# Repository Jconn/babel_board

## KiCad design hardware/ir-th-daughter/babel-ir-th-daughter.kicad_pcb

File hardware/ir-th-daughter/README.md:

# Babel IR TH daughter board — revision A (hand-solder)

A version of the [IR daughter](../ir-daughter/README.md) that can be built with
a soldering iron. Same host interface, outline, carrier holes and bench header;
the sensor is a through-hole MLX90614 in a TO-39 can, and every other part has
iron-friendly pads. Routed, DRC 0/0. OSH Park zip:
[`../fab/oshpark/babel-ir-th-daughter-revA-oshpark.zip`](../fab/oshpark/).

Open hardware under **CC BY-SA 3.0**, as an adaptation of the IR daughter; see
[LICENSE](LICENSE).

## What's the same as the IR daughter (rev C)

- J1 card edge, pinout and outline: VDD on contacts 3 and 18, GND on 1, 2, 8,
  19, 20; NVM bus on 5/6/7; sensor bus on 9/10. Reversible in the radio.
- J2 2x4 bench header, same pinout and position (see the IR daughter README).
- 24LC256 EEPROM at 0x50 with WP held high by R1; R2-R5 bus pull-ups DNP.
- 2 mm rounded body corners, chamfered tongue shoulders, carrier holes H1/H2.

## What's different

| | IR daughter rev C | IR TH daughter rev A |
| --- | --- | --- |
| Sensor | MLX90632 (3 x 3 mm leadless, bottom pad) | MLX90614ESF-BCC-000-TU (TO-39, 4 leads) |
| Sensor address | 0x3A | 0x5A (SMBus, 100 kHz max) |
| Accuracy | about ±0.2 °C (medical range) | about ±0.5 °C |
| Field of view | about 50° | 35° |
| Host maths | Host computes temperature from calibration data | Sensor reports object/ambient temperature directly |
| Passives | 0603 | 0805 hand-solder pads |
| ADDR resistor (R6) | Yes | None (address is in sensor EEPROM) |

The host must use an MLX90614 driver for this card; the MLX90632 driver does
not work with it. The sensor bus pins are unchanged, so the radio needs no
change.

## Circuit

- U1: MLX90614ESF-BCC-000-TU, 3 V part (2.6-3.6 V), gradient compensated,
  35° field of view. TO-39 pins (Melexis datasheet rev 021, figure 1): 1 SCL,
  2 SDA, 3 VDD, 4 VSS. The can connects only to VSS internally; nothing else
  touches it. KiCad `TO-39-4` pad numbers match the datasheet with the tab at
  the upper left, as silkscreened.
- C1 100 nF beside U1 pins 3/4 (Melexis recommends 100 nF close to the sensor).
- U2 24LC256 (SOIC-8, 1.27 mm pitch: easy with an iron), C2 at its supply pin,
  C3 1 µF at the port, R1 10k WP pull-up.

## Assembly by hand

What to buy (three boards plus spares, and the ESP32-S3 bench kit):
[purchase-bom.csv](purchase-bom.csv). `bom.csv` is the generated design BOM.

1. Start with the smallest parts: U2 (tack one corner pin, check alignment,
   then the rest), then the 0805 passives. Leave R2-R5 off unless this card
   will run on a bench host without pull-ups.
2. U1 last on the front: insert with the tab matching the silk notch, keep
   the can square to the board, solder from the back, and trim the leads flush
   (under 1 mm). The carrier's 10 mm relief hole sits behind the leads.
3. J2 only on bench cards; it does not fit the host boot or carrier.

Power from a current-limited 3.3 V supply first. An I2C scan should show 0x5A
(sensor) and 0x50 (EEPROM).

## Mechanical notes

- The TO-39 can stands about 4-5 mm off the front face (a can, not a flat
  package). Keep it clear of anything in front of the card and keep the 35°
  field of view open.
- Through-hole leads come out on the back inside the carrier's sensor relief.
- The boot-slot interference with U2/R1/C3 noted in `../ROUTING.md` applies to
  this board too (same positions).

## Checks and reproduction

```sh
K=squashfs-root/bin/kicad-cli; D=hardware/ir-th-daughter
python3 $D/tools/generate_schematic.py
$K sch erc $D/babel-ir-th-daughter.kicad_sch --exit-code-violations -o $D/erc-report.txt
$K sch export netlist $D/babel-ir-th-daughter.kicad_sch --format kicadxml -o $D/babel-ir-th-daughter.net.xml
python3 $D/tools/verify_netlist.py
$K pcb drc --schematic-parity --severity-error --severity-warning --format json \
    -o $D/layout-routing-drc.json $D/babel-ir-th-daughter.kicad_pcb
```

DRC: 0 violations, 0 unconnected, with the same two excluded J2 silk-corner
markers as the IR daughter. Schematic parity lists H1/H2 as board-only
footprints (carrier holes), as on the IR daughter.

Not tested: fabrication, hand assembly, sensor readings, carrier fit with the
TO-39 can.

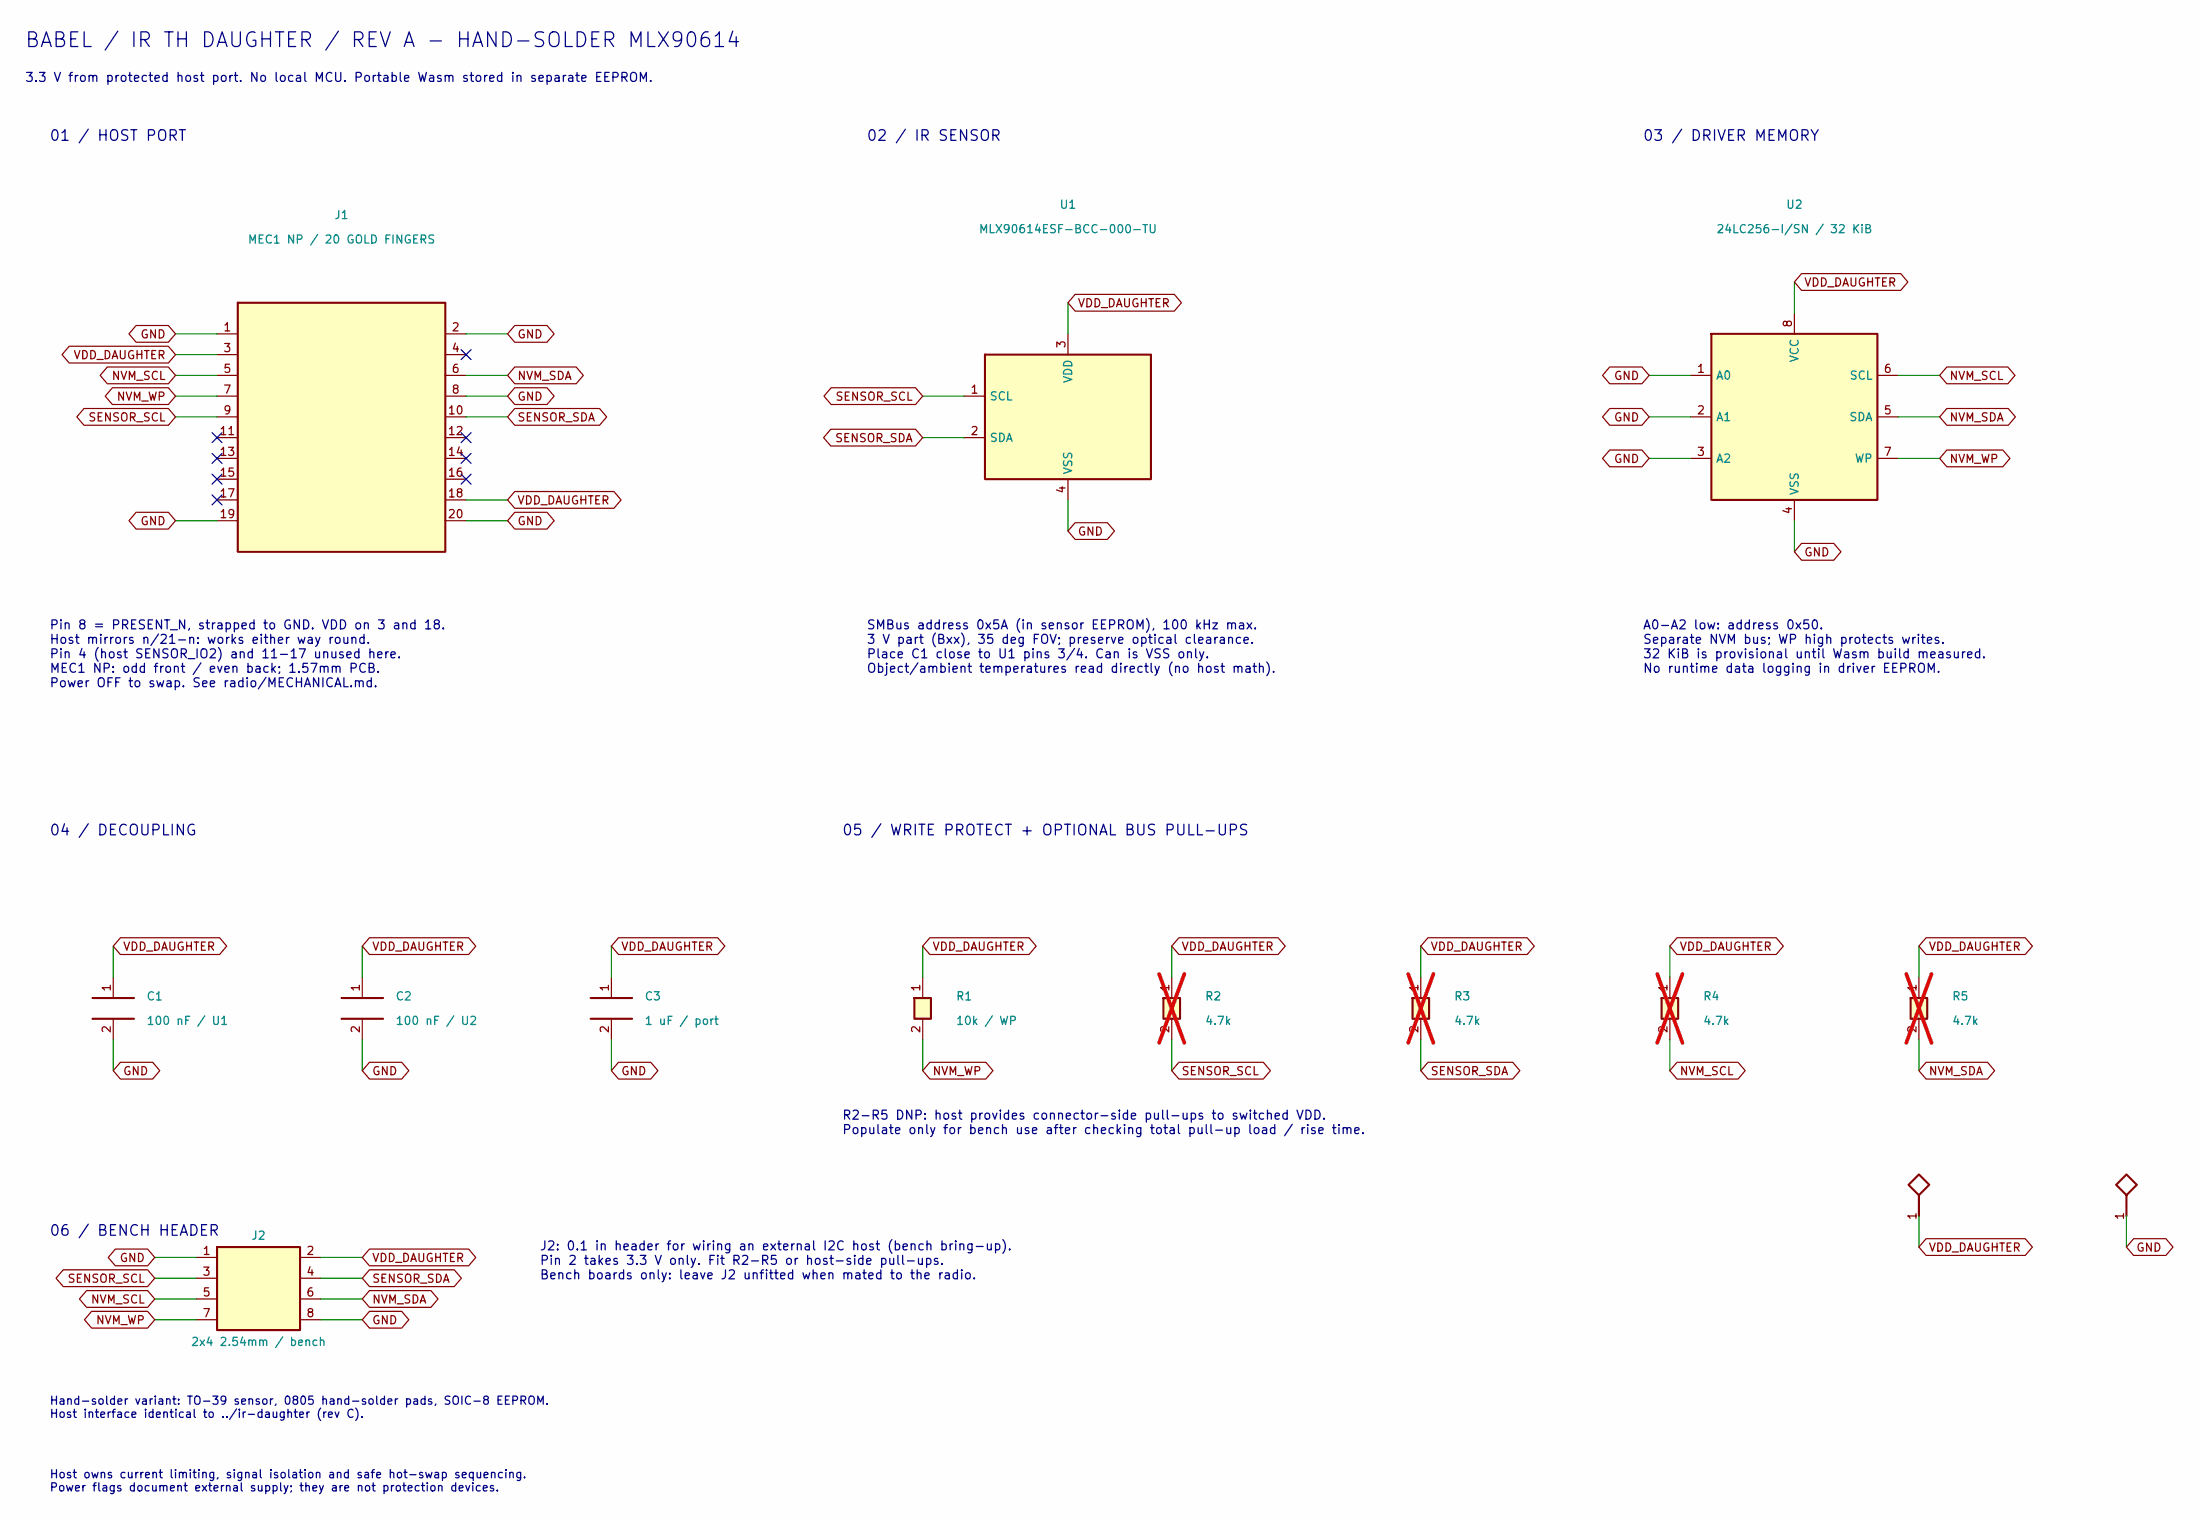
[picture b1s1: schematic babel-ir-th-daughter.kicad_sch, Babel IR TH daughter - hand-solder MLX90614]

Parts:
C1: 100 nF / U1; C_0805_2012Metric_Pad1.18x1.45mm_HandSolder
C2: 100 nF / U2; C_0805_2012Metric_Pad1.18x1.45mm_HandSolder
C3: 1 uF / port; C_0805_2012Metric_Pad1.18x1.45mm_HandSolder
J1: MEC1 NP / 20 GOLD FINGERS; MEC1_110_02_NP_Card
J2: 2x4 2.54mm / bench; PinHeader_2x04_P2.54mm_Vertical
R1: 10k / WP; R_0805_2012Metric_Pad1.20x1.40mm_HandSolder
R2, R3, R4, R5: 4.7k; R_0805_2012Metric_Pad1.20x1.40mm_HandSolder; not fitted
U1: MLX90614ESF-BCC-000-TU; TO-39-4
U2: 24LC256-I/SN / 32 KiB; SOIC-8_3.9x4.9mm_P1.27mm

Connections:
GND: C1.2, C2.2, C3.2, J1.1, J1.2, J1.8, J1.19, J1.20, J2.1, J2.8, U1.4 (VSS), U2.1 (A0), U2.2 (A1), U2.3 (A2), U2.4 (VSS)
NVM_SCL: J1.5, J2.5, R4.2, U2.6 (SCL)
NVM_SDA: J1.6, J2.6, R5.2, U2.5 (SDA)
NVM_WP: J1.7, J2.7, R1.2, U2.7 (WP)
SENSOR_SCL: J1.9, J2.3, R2.2, U1.1 (SCL)
SENSOR_SDA: J1.10, J2.4, R3.2, U1.2 (SDA)
VDD_DAUGHTER: C1.1, C2.1, C3.1, J1.3, J1.18, J2.2, R1.1, R2.1, R3.1, R4.1, R5.1, U1.3 (VDD), U2.8 (VCC)

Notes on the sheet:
BABEL / IR TH DAUGHTER / REV A - HAND-SOLDER MLX90614
3.3 V from protected host port. No local MCU. Portable Wasm stored in separate EEPROM.
01 / HOST PORT
02 / IR SENSOR
03 / DRIVER MEMORY
Pin 8 = PRESENT_N, strapped to GND. VDD on 3 and 18. Host mirrors n/21-n: works either way round. Pin 4 (host SENSOR_IO2) and 11-17 unused here. MEC1 NP: odd front / even back; 1.57mm PCB. Power OFF to swap. See radio/MECHANICAL.md.
SMBus address 0x5A (in sensor EEPROM), 100 kHz max. 3 V part (Bxx), 35 deg FOV; preserve optical clearance. Place C1 close to U1 pins 3/4. Can is VSS only. Object/ambient temperatures read directly (no host math).
A0-A2 low: address 0x50. Separate NVM bus; WP high protects writes. 32 KiB is provisional until Wasm build measured. No runtime data logging in driver EEPROM.
04 / DECOUPLING
05 / WRITE PROTECT + OPTIONAL BUS PULL-UPS
R2-R5 DNP: host provides connector-side pull-ups to switched VDD. Populate only for bench use after checking total pull-up load / rise time.
06 / BENCH HEADER
J2: 0.1 in header for wiring an external I2C host (bench bring-up). Pin 2 takes 3.3 V only. Fit R2-R5 or host-side pull-ups. Bench boards only: leave J2 unfitted when mated to the radio.
Host owns current limiting, signal isolation and safe hot-swap sequencing. Power flags document external supply; they are not protection devices.
Hand-solder variant: TO-39 sensor, 0805 hand-solder pads, SOIC-8 EEPROM. Host interface identical to ../ir-daughter (rev C).

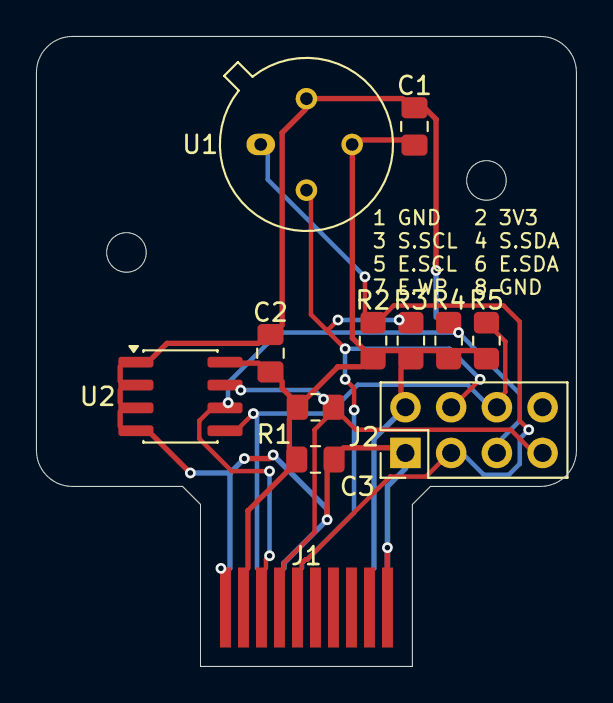
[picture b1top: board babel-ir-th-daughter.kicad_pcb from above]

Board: 2 copper layers, 30.0 x 35.0 mm, 14 parts (0 on the bottom side), 7 nets.

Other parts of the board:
H1, H2: M2 mechanical / NPTH

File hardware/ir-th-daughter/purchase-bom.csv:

Section,Refs,Qty per board,Buy qty,Description,Manufacturer,MPN,Notes
Board,U1,1,3,"IR thermometer, TO-39, 3 V, 35 deg FOV",Melexis,MLX90614ESF-BCC-000-TU,"Must be a -B (3 V) part. MLX90614ESF-BAA-000-TU (90 deg FOV) fits the same footprint. About $22-26 each in single units."
Board,U2,1,5,"256 Kbit I2C EEPROM, SOIC-8",Microchip,24LC256-I/SN,"24AA256-I/SN or 24FC256-I/SN also work at 3.3 V."
Board,"C1, C2",2,10,"100 nF 50 V X7R ceramic, 0805",Samsung,CL21B104KBCNNNC,Any 0805 X7R 100 nF >= 16 V.
Board,C3,1,10,"1 uF 25 V X7R ceramic, 0805",Samsung,CL21B105KAFNNNE,Any 0805 X7R 1 uF >= 10 V.
Board,R1,1,10,"10 k 1% resistor, 0805",Yageo,RC0805FR-0710KL,Any 0805 10 k.
Board,R2-R5,4,20,"4.7 k 1% resistor, 0805",Yageo,RC0805FR-074K7L,"DNP for cards used in the radio; fit all four on bench cards wired to the dev board."
Board,J2,1,1,"2.54 mm male header, 2x40 breakaway (cut to 2x4)",Sullins,PRPC040DAAN-RC,"One strip makes many 2x4 pieces. Fit J2 only on bench cards."
Bench,-,-,1,"ESP32-S3 dev board, WROOM-1 N8R8 (same module as the radio)",Espressif,ESP32-S3-DEVKITC-1-N8R8,"Not the -1U variant (external antenna). Also sold by Adafruit (product 5336)."
Bench,-,-,1,"USB cable for the dev board",-,-,"Match the board's ports (check the listing; recent revisions use USB-C)."
Bench,-,-,1,"Female-female Dupont jumper wires, 10-20 cm",-,-,"Six wires per card: GND, 3V3, SCL, SDA, WP and a spare GND."

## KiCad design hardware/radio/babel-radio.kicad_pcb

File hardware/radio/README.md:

# Babel radio/main board — revision D draft

Onboard charging restored by user decision on 2026-10-19. Revision D combines
the revision B charging guard with the connector, footprint and USB protection
work from the interrupted revision C. R90 remains DNP until bench qualification.
The [review note](REVIEW-2026-10-18-charging.md) is retained as historical context.

Baseline selected by the user: **ESP32-S3-WROOM-1-N8R8**. Alif excluded;
STM32N6 is not the current implementation. This board owns BLE, WAMR, display,
USB programming, power management, and one daughter port. No routing or
fabrication release is included.

Open [babel-radio.kicad_pro](babel-radio.kicad_pro) in KiCad 10, then its root
schematic. [PDF review copy](babel-radio.pdf), [review BOM](bom.csv), and
[GPIO allocation](gpio-map.csv) accompany the native files. Symbols are embedded
and also provided in the project-local library. The native
[PCB starting file](babel-radio.kicad_pcb) is ready for layout under the
[shared layout contract](../LAYOUT-PLAN.md). The generated fp-lib-table
uses the supplied AppDir footprint libraries; assigned pad-number sets are checked.
All 154 radio footprints are assigned. Critical custom land patterns have been
dimensionally screened; physical mating and assembly checks remain. Circuit
parts staged outside the outline are unplaced, not a finished PCB layout.

## Sheets

1. Overview and release blockers.
2. Host: WROOM, EN delay, boot/reset/user buttons, 3.3 V SPI display-module header,
   and UART recovery header. GPIO35/36/37 are unavailable on the R8 module.
3. USB-C USB2 device input, USB data ESD, BQ24079 4.1 V charger/power path,
   and protected battery/NTC connector.
4. TPS63070 3.3 V buck-boost, reference-topology filter, feedback and system switch.
5. TPS2553 daughter power limit and hardware presence/request gating.
6. Card edge, dedicated NVM isolation, sensor isolation and switched-rail pull-ups.
7. Autonomous USB-C permission detection, gated power input and USB data switch.
8. Hardware charge-temperature window, timer and battery-startup supervision.
9. Sixteen bring-up test points (including two ground references).

J1 contact numbers match the IR daughter electrical contract and assigned Samtec
NP mating footprints. See [MECHANICAL.md](MECHANICAL.md). SENSOR_TX means host TX, daughter RX.
H_ prefixes are MCU-side nets; unprefixed sensor/NVM names are connector-side.
Net labels connect across sheets. An NC cross is intentional, not an unfinished wire.

## Power and battery precautions

### Selected battery and integration status

User selection: **Jauch LP523450JU+PCM+JST PHR-3 70MM**, Jauch number
**251555**, protected 1S pouch pack, 3.7 V nominal, 4.2 V maximum, 1000 mAh typical.
The [pack specification](https://mm.digikey.com/Volume0/opasdata/d220001/medias/docus/5702/LP523450JU%20251555.pdf)
specifies 53 x 34.5 x 5.4 mm at delivery, up to 5.8 mm thick after cycling,
and a 10k NTC (B3435). Allow additional enclosure/retention clearance.

J5 now matches the pack's 1 red positive, 2 yellow NTC, 3 black negative.
The mating header is JST B3B-PH-K-S; verify its physical pin-1 orientation
against the actual harness before connection.
R12 is now 5.36k 1%: approximately 166 mA nominal, at most 184 mA using
TI's maximum 975 A-ohm factor and minimum resistor tolerance. This is below
190 mA (0.2C using the pack's minimum 950 mAh capacity) for its cold-temperature
charge-current limit. U20 now provides a separate hardware temperature window.
Keep R90 DNP until physical qualification.

The original direct-NTC connection failed margin screening and has been replaced.
Run `python3 hardware/radio/tools/audit_charge_limits.py` for current, voltage,
timer and temperature checks. The new window cuts off nominally below 10.7 C
or above 40.0 C. Screened cutoff corners are 7.1..13.7 C and 37.2..43.3 C,
including an ASSUMED +/-5% beta spread. The actual pack curve, thermal lag,
startup and fault behavior must still be qualified; this is not certification.

Provide a mechanically protective battery compartment with an insulating
barrier from solder joints, screw tips and hot components. Protection electronics
do not prevent puncture or external heating. Disconnect and remove the pack
during soldering/rework. Initial electrical bring-up should use a current-limited
supply without the pack, using a valid USB-C current advertisement.

**Charging is disabled in the default BOM: R90 is DNP.** Do not fit R90 until the
cell, its protection, permitted charge current, connector polarity, NTC curve,
charging temperature limits, and board thermals have been reviewed. R90 is a
hardware assembly option, not a firmware control. Never use an unprotected cell.
The charger is not battery overcurrent/undervoltage protection. The selected pack
is a protected 1S 4.2 V Li-ion, 1000 mAh typical, with a 10k NTC connected to
pack negative. A two-wire pack is not a drop-in replacement. The NTC is measured
by U20, independently of the processor, and controls charger CE through U22/U23.
The charger's original TS input has a fixed 10k bias because it no longer performs
pack-temperature sensing. Never bypass U20 or connect R90 directly to ground.

- BQ24079 replaces BQ24074: nominal 4.1 V charging (maximum 4.141 V) leaves
  margin below the pack's 4.2 V limit. This deliberately reduces usable capacity.
  It is NOT the voltage-based-TS BQ24079T variant. CE is pin 4; SYSOFF pin 15 is low.
- R108 = 71.5k 0.1% sets nominal 9.53-hour fast-charge and 57.2-minute precharge
  timers. Fast-charge tolerance is 7.14..11.93 hours before dynamic extensions.
  Current taper and actual pack capacity need bench testing for completion.
  Timer expiry is a fault, not permission to repeatedly restart charging.
  External-temperature CE cycling resets the timer; this is NOT a cumulative
  wall-clock charge watchdog. Firmware should report faults and avoid retries.
- USB-C-only policy: require 5 V and advertised 1.5 A or 3 A. U15/U16 run before
  the main rail; U18 gates input power and U19 gates data. R13 sets nominal
  904 mA charger input, at most 976 mA, leaving margin for the CC circuitry.
  Default-current USB-C and USB-A adapters are unsupported and cannot charge.
  Native USB programming additionally needs a data-capable C-to-C connection.
  See [USB-STARTUP.md](USB-STARTUP.md). No USB PD negotiation or USB host mode.
- GPIO3/45 now remain pulled-low reserved straps, disconnected from charger
  control. GPIO48 still senses accepted charger input via USB_PGOOD_N.
- U21 screens battery voltage before main-rail startup; USB permission can start
  the main rail with no battery. The battery threshold is approximately 3.33 V,
  with hysteresis but no removal/undervoltage latch. Test near-empty cycling.
- System switch SW4 disables the buck-boost, not charging. Off is not a physical
  battery disconnect. The pack must protect against deep discharge.
- TPS63070 feedback: 0.8*(1+470/150) = 3.307 V nominal. Regulator transient and
  thermal margins are not yet measured. Capacitor DC-bias derating matters.
- Daughter power: 226k 1% on TPS2553 gives TI's nominal 120 mA setting, with
  documented 101.3–142.1 mA limits; continuous daughter budget stays 100 mA.
- J3 VTREF is for a 3.3 V UART adapter's voltage reference, not a second power
  input. Do not backfeed the rail or connect RS-232-level signals.

## Port sequencing and limitations

Prototype operation requires SW4 OFF before daughter insertion/removal. Hot
swapping remains a qualification target, not a supported untested operating mode.

Hardware equations:

```
PORT_EN     = !PRESENT_N && PWR_REQ
NVM_OE_N    = !(PORT_EN && NVM_REQ)
SENSOR_OE_N = !(PORT_EN && SENSOR_REQ)
```

All requests have pulldowns; switch OEs have pull-ups. The MCU resets with the
port isolated and unpowered. Removal detection forces these gates off without
waiting for the Wasm driver. This is not a guarantee of early removal detection:
the exact card-edge contact lengths, ground-first behavior, bounce and partial
insertion must still be designed and tested. Firmware must clear requests on
presence loss before a new attachment; the gates are not a removal latch.

Boot/attach: keep requests low and GPIOs high impedance, debounce presence,
enable power, wait for validated settling, enable NVM only, validate the image,
configure the selected sensor peripheral, then enable sensor isolation.
Removal/fault: clear sensor/NVM requests and power, cancel transactions, invalidate
readings, and require a fresh attachment/retry sequence. Disable internal MCU
pull-ups before disconnecting. WP and reset controls are open-drain.

### Reversible daughter connector (2026-10-22)

J1 is wired so a daughter works inserted either way round. A reversed card puts
its contact n on socket contact 21-n, so each mirrored pair carries one net:

| Contacts | Net | Contacts | Net |
| --- | --- | --- | --- |
| 1 / 20 | GND | 6 / 15 | NVM_SDA |
| 2 / 19 | GND | 7 / 14 | NVM_WP |
| 3 / 18 | VDD_DAUGHTER | 8 / 13 | PRESENT_N |
| 4 / 17 | SENSOR_IO2 | 9 / 12 | SENSOR_IO0 |
| 5 / 16 | NVM_SCL | 10 / 11 | SENSOR_IO1 |

The cost is the dedicated SPI, UART and RESET contacts. What remains for the
sensor is three general lines, SENSOR_IO0-2, each an ESP32-S3 GPIO (7, 8, 15)
routed through the GPIO matrix, the U13 bus switch and one ESD channel, so the
protocol is the firmware's choice:

| Daughter interface | IO0 | IO1 | IO2 |
| --- | --- | --- | --- |
| I2C + interrupt | SCL | SDA | IRQ (open-drain, active low) |
| UART | host TX | host RX | spare / IRQ |
| 3-wire SPI | SCK | SDIO (bidirectional) | CS |
| Read-only SPI | SCK | MISO | CS |

Full 4-wire SPI (separate MOSI and MISO) does not fit. IO0/IO1 keep 4.7k and
IO2 10k pull-ups to VDD_DAUGHTER: harmless for push-pull SPI/UART (about 0.7 mA
while a 4.7k line is low), and they hold an SPI chip select inactive by default.
Removed with the dedicated contacts: U14, C26, R36/R38 (CS_N/RESET_N
pull-ups), R120..R123 (0-ohm tuning sites), U34..U36 (ESD), and the ESP32
assignments of GPIO9-14 and GPIO16, which are now free. Retired references are
not reused. A daughter should tie each pair it uses (or leave the mirror
contact open, as the IR daughter does for 4 and 11-17); it must never put a
different net on n and 21-n. `tools/verify_netlist.py` asserts the symmetry.

U13 isolates SENSOR_IO0-2 behind one enable; its other channels are unused. EEPROM isolation (U12) remains independent.

The switches do not recover a stuck I2C bus. Host transactions need deadlines
and recovery; EEPROM isolation is independent of sensor isolation. The rail's
10k bleeder gives passive discharge, not an active discharge or power-good check.
TPS2553 fault reporting is to firmware; no fault latch is provided. Verify
auto-retry, voltage collapse, signal back-powering and removal transients.

USB data, CC and every card-edge signal net (seven nets, one channel each; mirrored contacts share it) have ESD devices.
VBUS now has a 1.5 A fuse and SMBJ6.0A TVS; U18 is TPS22810DBVR with a 27 nF
slew-control capacitor. The higher-voltage switch replaces TPS22919 so the
TVS clamp is not applied to a 6 V-rated switch. U2 is now ground-referenced
TPD2E2U06 rather than USBLC6-2. Protection coordination and physical ESD return
paths still need review and measurement; this is not sustained overvoltage protection.
IC ratings do not constitute system-level ESD qualification.

## Selected display and mechanical integration

User selection: **[Adafruit 4741](https://www.adafruit.com/product/4741)**,
1.5-inch 128x128 OLED, SSD1327, 16-level grayscale (not color), using SPI.
Use the complete breakout with its onboard regulator and OLED boost converter,
not a bare panel. A full 4-bit framebuffer occupies 8192 bytes. Include idle
display blanking in firmware to reduce OLED wear.

The [Adafruit pinout guide](https://learn.adafruit.com/adafruit-grayscale-1-5-128x128-oled-display/pinouts)
requires cutting the breakout's J1 and J2 jumper traces to select SPI; these
jumper names are unrelated to Babel's connector references. It ships in I2C mode.

Babel J2 is a keyed JST PH adapter header, not a pin-for-pin module connector:
1 power (to module Vin), 2 ground, 3 clock, 4 MOSI, 5 CS,
6 D/C, 7 reset, 8 reserved NC. No touchscreen, MISO, or PWM brightness control is
allocated. OLED needs no backlight; schematic notes now identify the selected
module. Existing LCD_* net names are retained to avoid needless renaming.
The source CAD outline, mounting pattern and exact cable mapping are recorded in
[DISPLAY-INTEGRATION.md](DISPLAY-INTEGRATION.md). Physical stack height, cable
clearance and measured power budget still need checking before layout.

J4 is GCT USB4105-GF-A, with SH shield pads mapped to ground; J5 is selected above.
J1, switches, regulator and L1 now have assigned footprints. All
assigned footprints still need pad/dimension review. The WROOM antenna needs
Espressif's keepout and suitable placement away from battery/display metal.

## Verification and reproduction

See [PRE-LAYOUT.md](PRE-LAYOUT.md) for the ordered release checklist and progress.
See [FEATURES.md](FEATURES.md) for supported design paths and qualification limits.

Run from repository root with the supplied KiCad CLI:

```sh
python3 hardware/radio/tools/generate_footprints.py
python3 hardware/radio/tools/generate_schematic.py
squashfs-root/bin/kicad-cli sch erc hardware/radio/babel-radio.kicad_sch --exit-code-violations -o hardware/radio/erc-report.txt
squashfs-root/bin/kicad-cli sch export netlist hardware/radio/babel-radio.kicad_sch --format kicadxml -o hardware/radio/babel-radio.net.xml
python3 hardware/radio/tools/verify_netlist.py
python3 hardware/radio/tools/audit_charge_limits.py
python3 hardware/radio/tools/check_power_policy.py
python3 hardware/radio/tools/check_footprints.py
squashfs-root/bin/kicad-cli sch export pdf hardware/radio/babel-radio.kicad_sch -o hardware/radio/babel-radio.pdf
```

The generator overwrites the schematic, library, BOM and generated manifest;
reconcile manual edits first. Existing project settings are preserved. The checker
compares exported connectivity with the manifest and independently checks key IC
pin maps, reserved GPIOs, charge-disable assembly, isolation paths and the existing
IR daughter's J1. ERC uses normal KiCad defaults, with no project-specific waivers.
Neither test proves analog behavior, footprint correctness, battery safety, RF
performance or successful hot swapping. WAMR/BLE hardware bring-up remains undone.

## Design references

- [Espressif module datasheet](https://www.espressif.com/sites/default/files/documentation/esp32-s3-wroom-1_wroom-1u_datasheet_en.pdf), pin table and R8 restrictions.
- [Espressif schematic guidance](https://docs.espressif.com/projects/esp-hardware-design-guidelines/en/latest/esp32s3/schematic-checklist.html), EN and USB.
- [BQ2407x family including BQ24079](https://www.ti.com/lit/ds/symlink/bq24074.pdf), pin table and charge settings.
- [TPS3700](https://www.ti.com/lit/ds/symlink/tps3700.pdf), comparator limits and hysteresis.
- [TPS709](https://www.ti.com/lit/ds/symlink/tps709.pdf), always-on CC/NTC supply.
- [TUSB320LAI](https://www.ti.com/lit/ds/symlink/tusb320lai.pdf), sink-only GPIO mode and internal Rd.
- [TPS22810](https://www.ti.com/lit/ds/symlink/tps22810.pdf), input gating and slew control.
- [TS3USB221A](https://www.ti.com/lit/ds/symlink/ts3usb221a.pdf), data disconnect and powered-off leakage.
- [TPD2E2U06](https://www.ti.com/lit/ds/symlink/tpd2e2u06.pdf), 3-pin DCK variant, connector protection.
- [TPS63070](https://www.ti.com/lit/ds/symlink/tps63070.pdf), pin table and adjustable-output reference BOM. RNM has 15 numbered pads; do not invent a generic extra exposed pad.
- [TPS2553](https://www.ti.com/lit/ds/symlink/tps2553.pdf), DBV pinout and Table 2 current-limit tolerances.
- [SN74CB3Q3245](https://www.ti.com/lit/ds/symlink/sn74cb3q3245.pdf), isolation and powered-off behavior;
  [TI pin diagram](https://www.ti.com.cn/document-viewer/cn/SN74CB3Q3245/datasheet).
- [SN74LVC1G08](https://www.ti.com/lit/ds/symlink/sn74lvc1g08.pdf), [SN74LVC1G04](https://www.ti.com/lit/ds/symlink/sn74lvc1g04.pdf), DBV pin tables.
- [SN74LVC1G06](https://www.ti.com/lit/ds/symlink/sn74lvc1g06.pdf), open-drain charger-disable control.

The WROOM stock check from the preceding evaluation supports small-quantity
prototype sourcing, not a lifetime supply guarantee. The complete supporting BOM
has not yet been stock-qualified. Do not order from this review BOM as a kit.

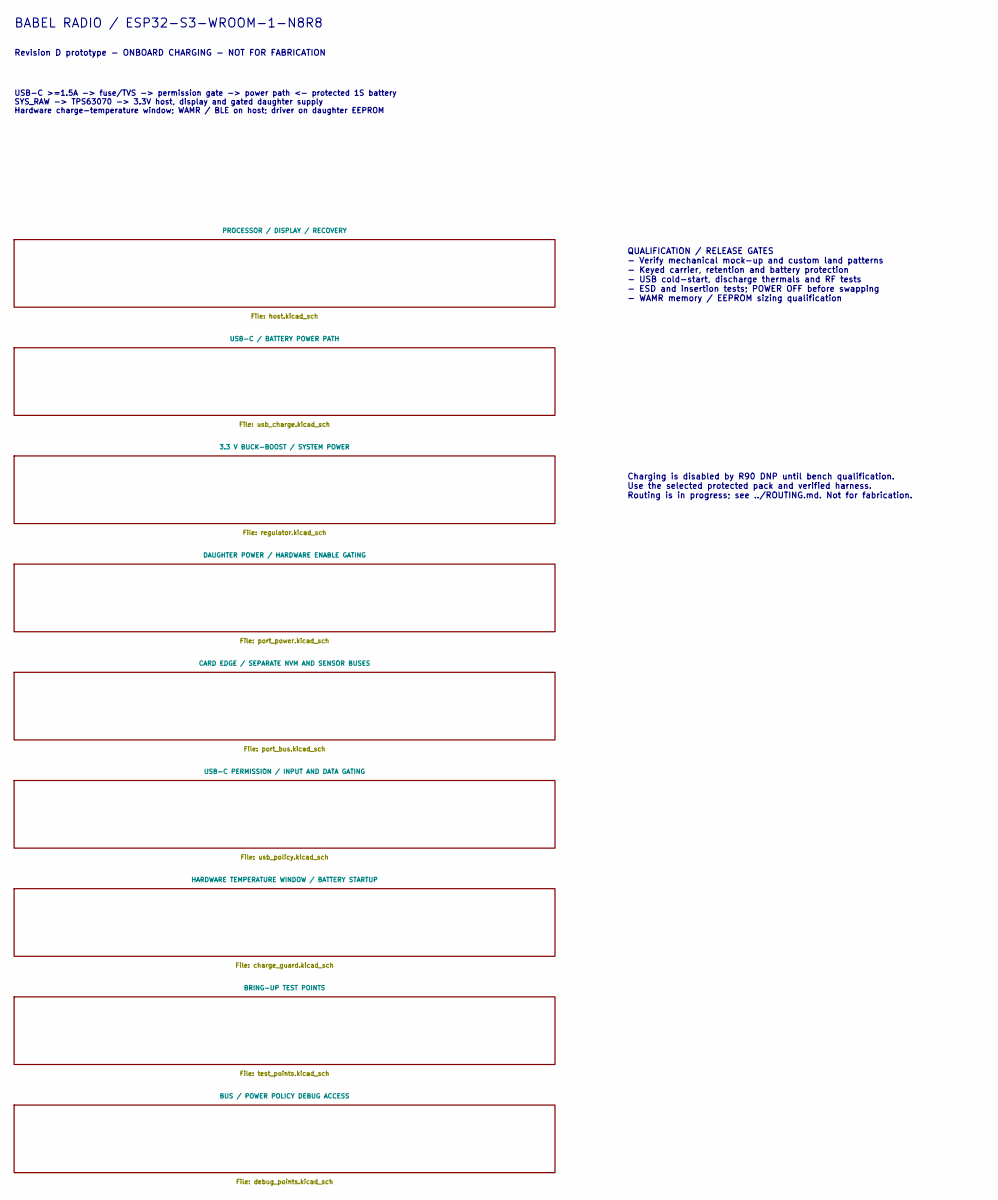
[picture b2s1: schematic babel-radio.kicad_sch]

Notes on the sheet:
BABEL RADIO / ESP32-S3-WROOM-1-N8R8
Revision D prototype - ONBOARD CHARGING - NOT FOR FABRICATION
USB-C >=1.5A -> fuse/TVS -> permission gate -> power path <- protected 1S battery SYS_RAW -> TPS63070 -> 3.3V host, display and gated daughter supply Hardware charge-temperature window; WAMR / BLE on host; driver on daughter EEPROM
QUALIFICATION / RELEASE GATES - Verify mechanical mock-up and custom land patterns - Keyed carrier, retention and battery protection - USB cold-start, discharge thermals and RF tests - ESD and insertion tests; POWER OFF before swapping - WAMR memory / EEPROM sizing qualification
Charging is disabled by R90 DNP until bench qualification. Use the selected protected pack and verified harness. Routing is in progress; see ../ROUTING.md. Not for fabrication.

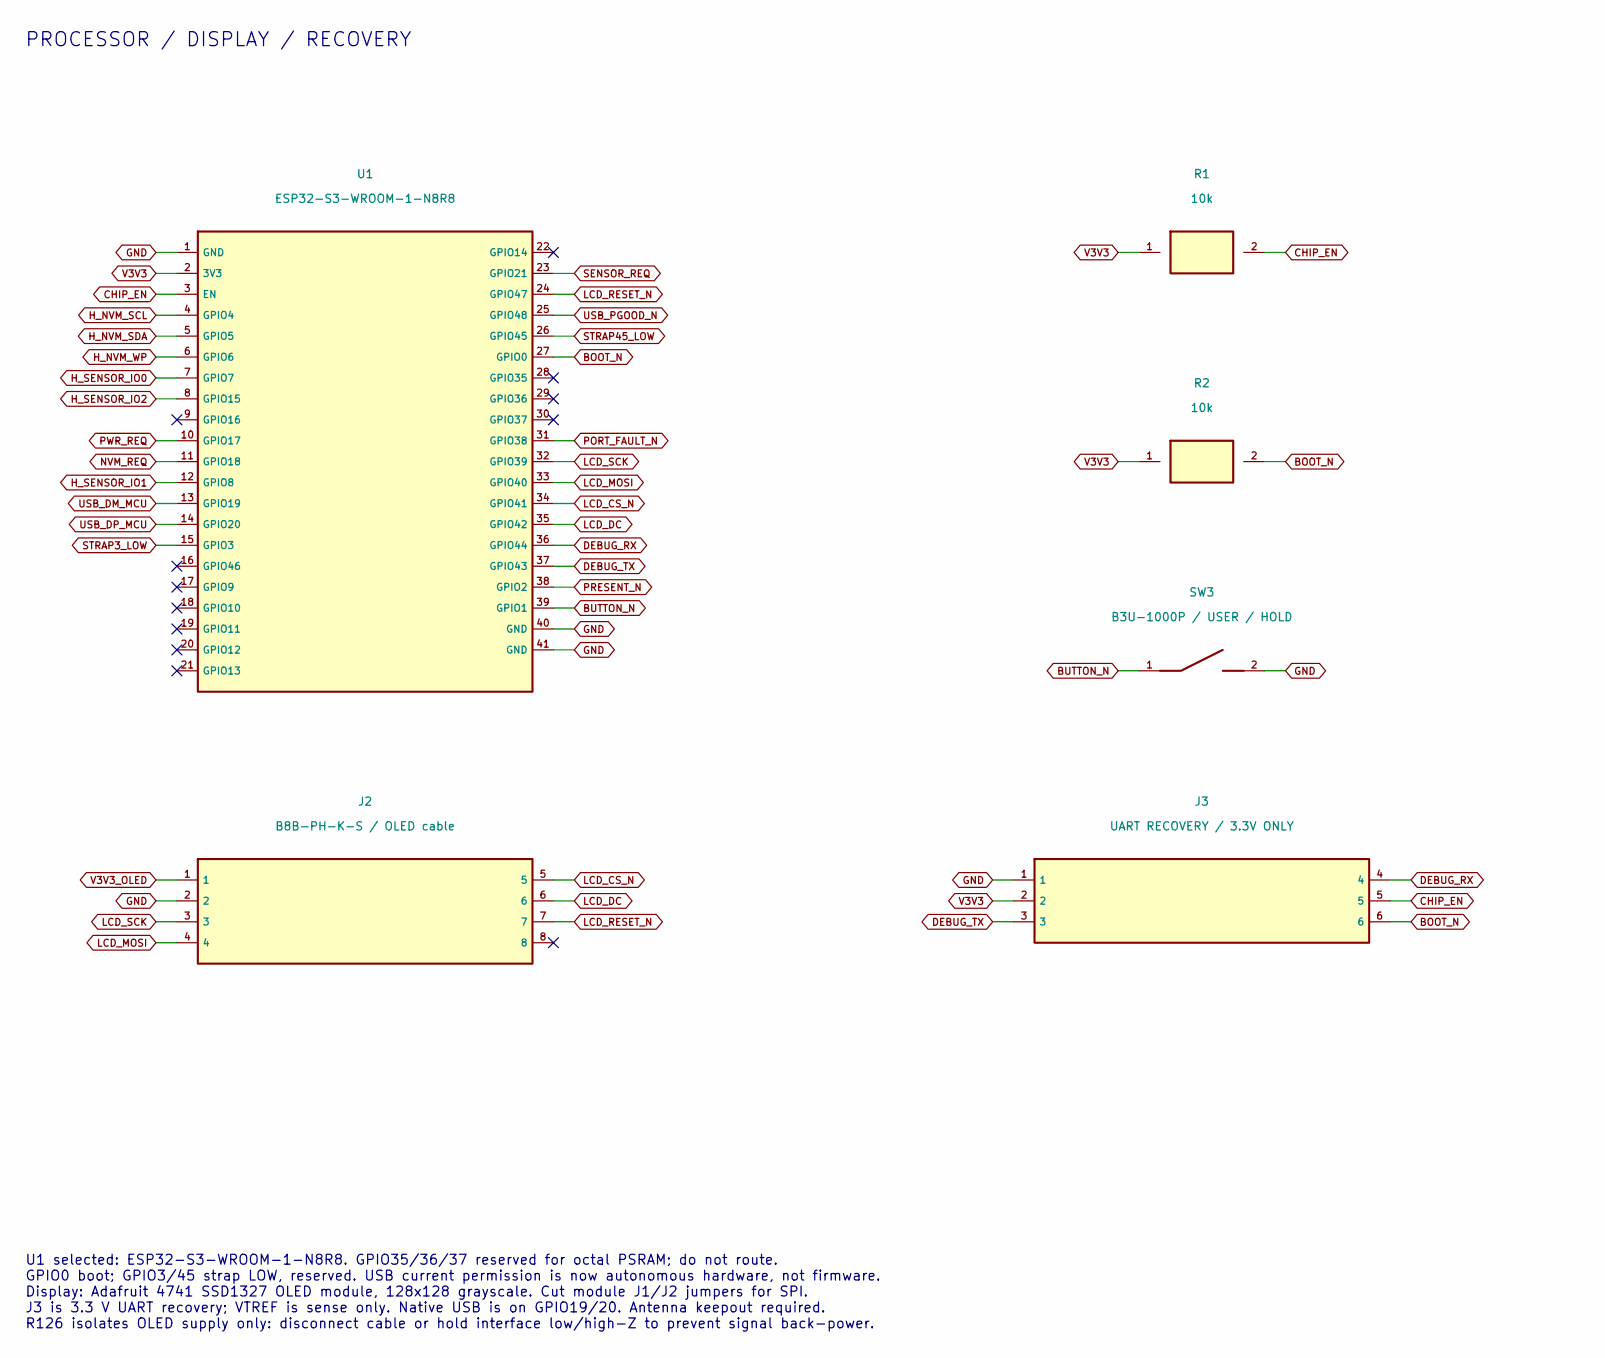
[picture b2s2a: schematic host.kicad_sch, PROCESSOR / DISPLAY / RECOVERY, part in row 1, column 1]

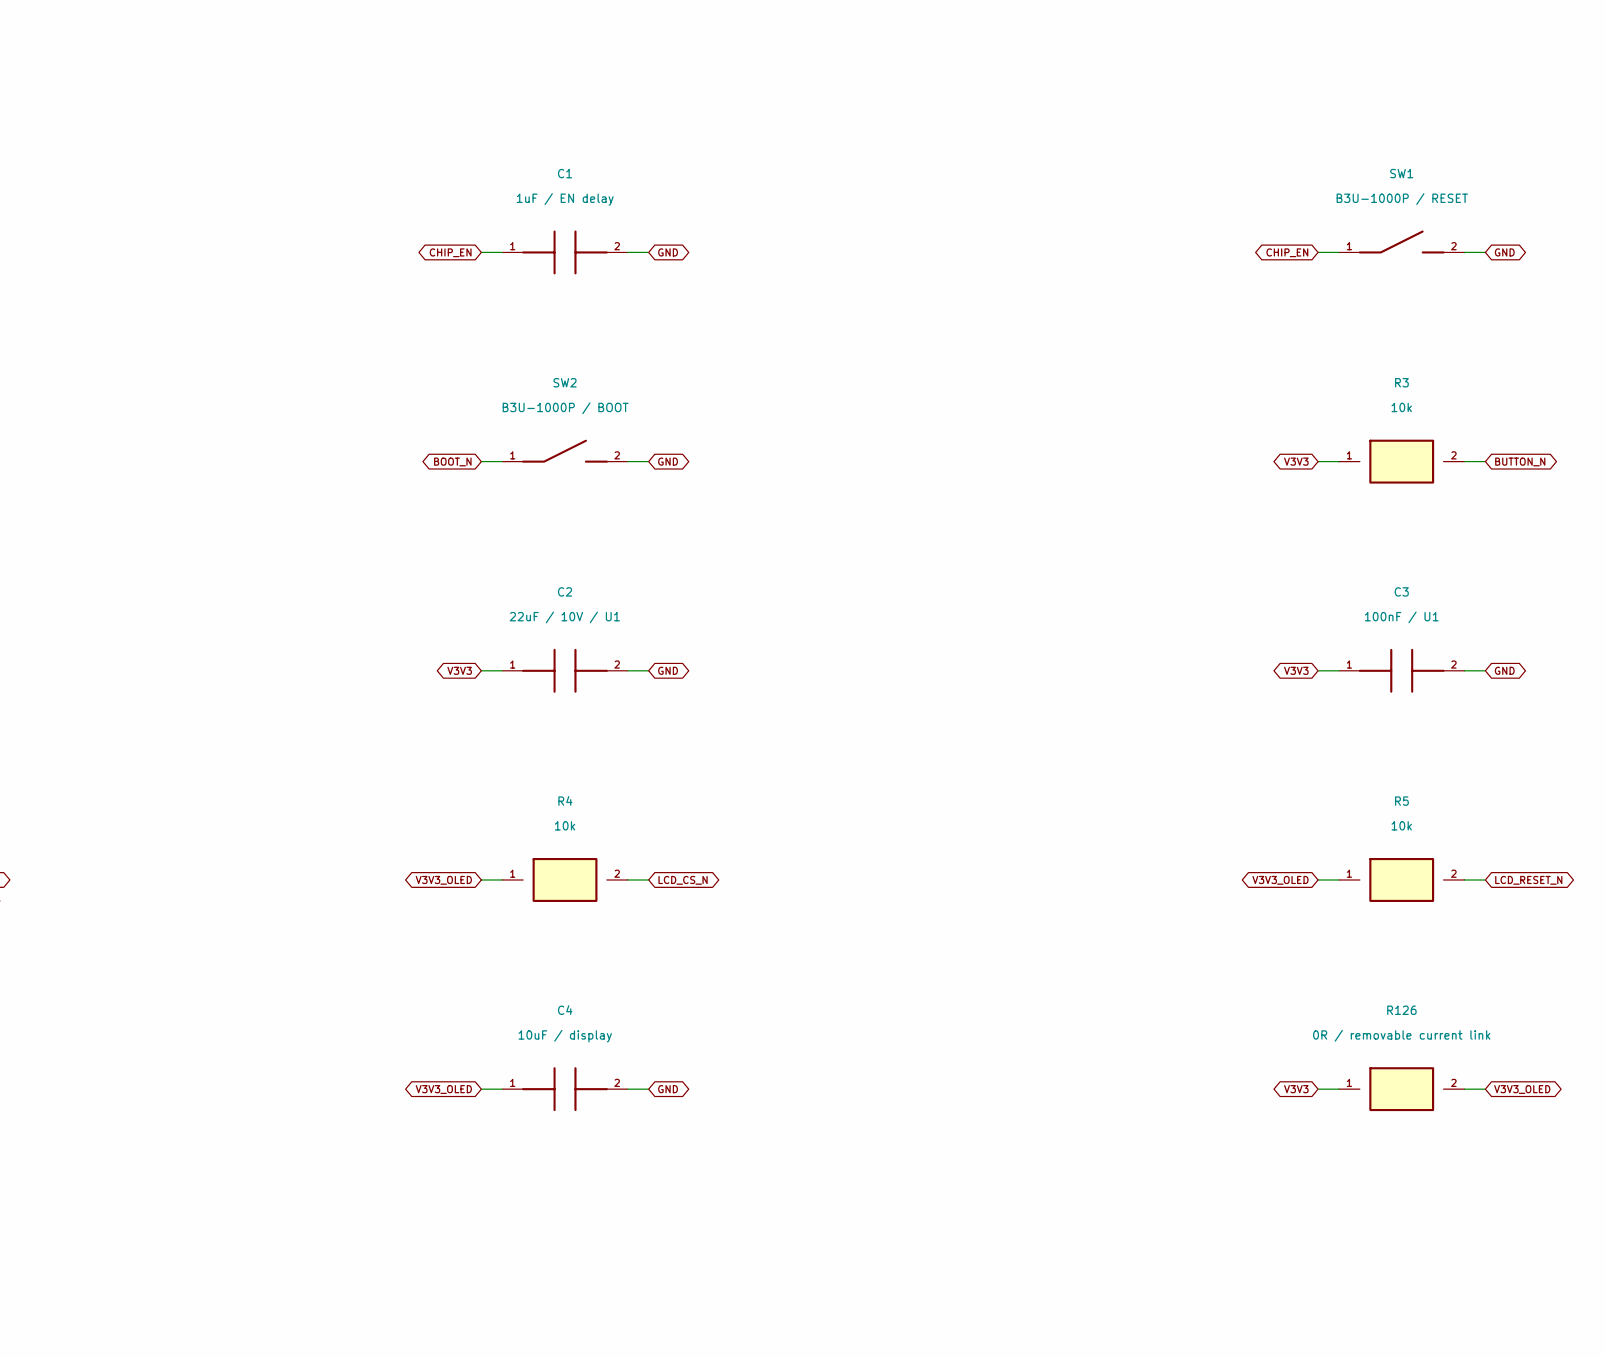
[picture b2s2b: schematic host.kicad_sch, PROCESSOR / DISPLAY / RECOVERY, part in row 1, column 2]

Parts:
C1: 1uF / EN delay; C_0805_2012Metric
C2: 22uF / 10V / U1; C_0805_2012Metric
C3: 100nF / U1; C_0805_2012Metric
C4: 10uF / display; C_0805_2012Metric
J2: B8B-PH-K-S / OLED cable; JST_PH_B8B-PH-K_1x08_P2.00mm_Vertical
J3: UART RECOVERY / 3.3V ONLY; PinHeader_1x06_P2.54mm_Vertical
R1, R2, R3, R4, R5: 10k; R_0603_1608Metric
R126: 0R / removable current link; R_0603_1608Metric
SW1: B3U-1000P / RESET; SW_SPST_B3U-1000P
SW2: B3U-1000P / BOOT; SW_SPST_B3U-1000P
SW3: B3U-1000P / USER / HOLD; SW_SPST_B3U-1000P
U1: ESP32-S3-WROOM-1-N8R8; ESP32-S3-WROOM-1

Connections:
BOOT_N: J3.6, R2.2, SW2.1, U1.27 (GPIO0)
BUTTON_N: R3.2, SW3.1, U1.39 (GPIO1)
CHIP_EN: C1.1, J3.5, R1.2, SW1.1, U1.3 (EN)
DEBUG_RX: J3.4, U1.36 (GPIO44)
DEBUG_TX: J3.3, U1.37 (GPIO43)
GND: C1.2, C2.2, C3.2, C4.2, J2.2, J3.1, SW1.2, SW2.2, SW3.2, U1.1 (GND), U1.40 (GND), U1.41 (GND); also elsewhere on the board
H_NVM_SCL: U1.4 (GPIO4); also elsewhere on the board
H_NVM_SDA: U1.5 (GPIO5); also elsewhere on the board
H_NVM_WP: U1.6 (GPIO6); also elsewhere on the board
H_SENSOR_IO0: U1.7 (GPIO7); also elsewhere on the board
H_SENSOR_IO1: U1.12 (GPIO8); also elsewhere on the board
H_SENSOR_IO2: U1.8 (GPIO15); also elsewhere on the board
LCD_CS_N: J2.5, R4.2, U1.34 (GPIO41)
LCD_DC: J2.6, U1.35 (GPIO42)
LCD_MOSI: J2.4, U1.33 (GPIO40)
LCD_RESET_N: J2.7, R5.2, U1.24 (GPIO47)
LCD_SCK: J2.3, U1.32 (GPIO39)
NVM_REQ: U1.11 (GPIO18); also elsewhere on the board
PORT_FAULT_N: U1.31 (GPIO38); also elsewhere on the board
PRESENT_N: U1.38 (GPIO2); also elsewhere on the board
PWR_REQ: U1.10 (GPIO17); also elsewhere on the board
SENSOR_REQ: U1.23 (GPIO21); also elsewhere on the board
STRAP3_LOW: U1.15 (GPIO3); also elsewhere on the board
STRAP45_LOW: U1.26 (GPIO45); also elsewhere on the board
USB_DM_MCU: U1.13 (GPIO19); also elsewhere on the board
USB_DP_MCU: U1.14 (GPIO20); also elsewhere on the board
USB_PGOOD_N: U1.25 (GPIO48); also elsewhere on the board
V3V3: C2.1, C3.1, J3.2, R1.1, R2.1, R3.1, R126.1, U1.2 (3V3); also elsewhere on the board
V3V3_OLED: C4.1, J2.1, R4.1, R5.1, R126.2

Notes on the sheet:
PROCESSOR / DISPLAY / RECOVERY
U1 selected: ESP32-S3-WROOM-1-N8R8. GPIO35/36/37 reserved for octal PSRAM; do not route. GPIO0 boot; GPIO3/45 strap LOW, reserved. USB current permission is now autonomous hardware, not firmware. Display: Adafruit 4741 SSD1327 OLED module, 128x128 grayscale. Cut module J1/J2 jumpers for SPI. J3 is 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
